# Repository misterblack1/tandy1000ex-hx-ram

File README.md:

# Tandy 1000 RAM Expansion

***Cheap*** *and **Simple** expansion board that only requires* <br>
*3 to 4 ICs and has been tested for **EX** and **HX** machines.*

*Designed by **[Adrian Black]**.*

<br>

<div align = center>

---

[![Button Video]][Video]   
[![Button PCB]][PCB]   
[![Button Schematic]][Schematic]   
[![Button Gerber]][Gerber]

---

<br>
<br>
<br>

![Preview]

<br>

⸢ *[Render]*  ⸥                                                                                           ⸢ *[Circuit]*  ⸥

</div>

<br>
<br>

## Assembly

*How to put the board together.*

<br>

### 3 ICs

If you bypass the  `74LS245`  with <br>
a jumper you can save one **IC**.

<br>

### LED

If you don't want the **LED**, you <br>
can leave it off as well as  `R3` .

<br>

### 74HCT

If you choose to use the  `74HCT` , you will <br>
just have to replace  `R1`  &  `R2`  with  `10kΩ` .

<br>
<br>

## Files

Created with **[KiCAD v5.1.4-1][KiCAD]**.

The uploaded files are of  `version 1.2` , with <br>
the fixes, talked about in the **[Video]**, applied.

<br>

<!----------------------------------------------------------------------------->

[Adrian Black]: https://github.com/misterblack1

[Video]: https://www.youtube.com/watch?v=l3RWOZX58A8
[KiCAD]: https://www.kicad.org/

[Schematic]: Resources/Schematics.pdf
[Preview]: Resources/Preview.png
[Circuit]: Resources/Circuit.png
[Render]: Resources/Render.png
[Gerber]: Gerbers
[PCB]: Source

<!-------------------------------[ Buttons ]----------------------------------->

[Button Schematic]: https://img.shields.io/badge/Schematic-006241?style=for-the-badge&logoColor=white&logo=StackShare
[Button Gerber]: https://img.shields.io/badge/Gerber-139BB4?style=for-the-badge&logoColor=white&logo=Stimulus
[Button Video]: https://img.shields.io/badge/Video-CD2640?style=for-the-badge&logoColor=white&logo=YouTube
[Button PCB]: https://img.shields.io/badge/PCB-314CB0?style=for-the-badge&logoColor=white&logo=tmux

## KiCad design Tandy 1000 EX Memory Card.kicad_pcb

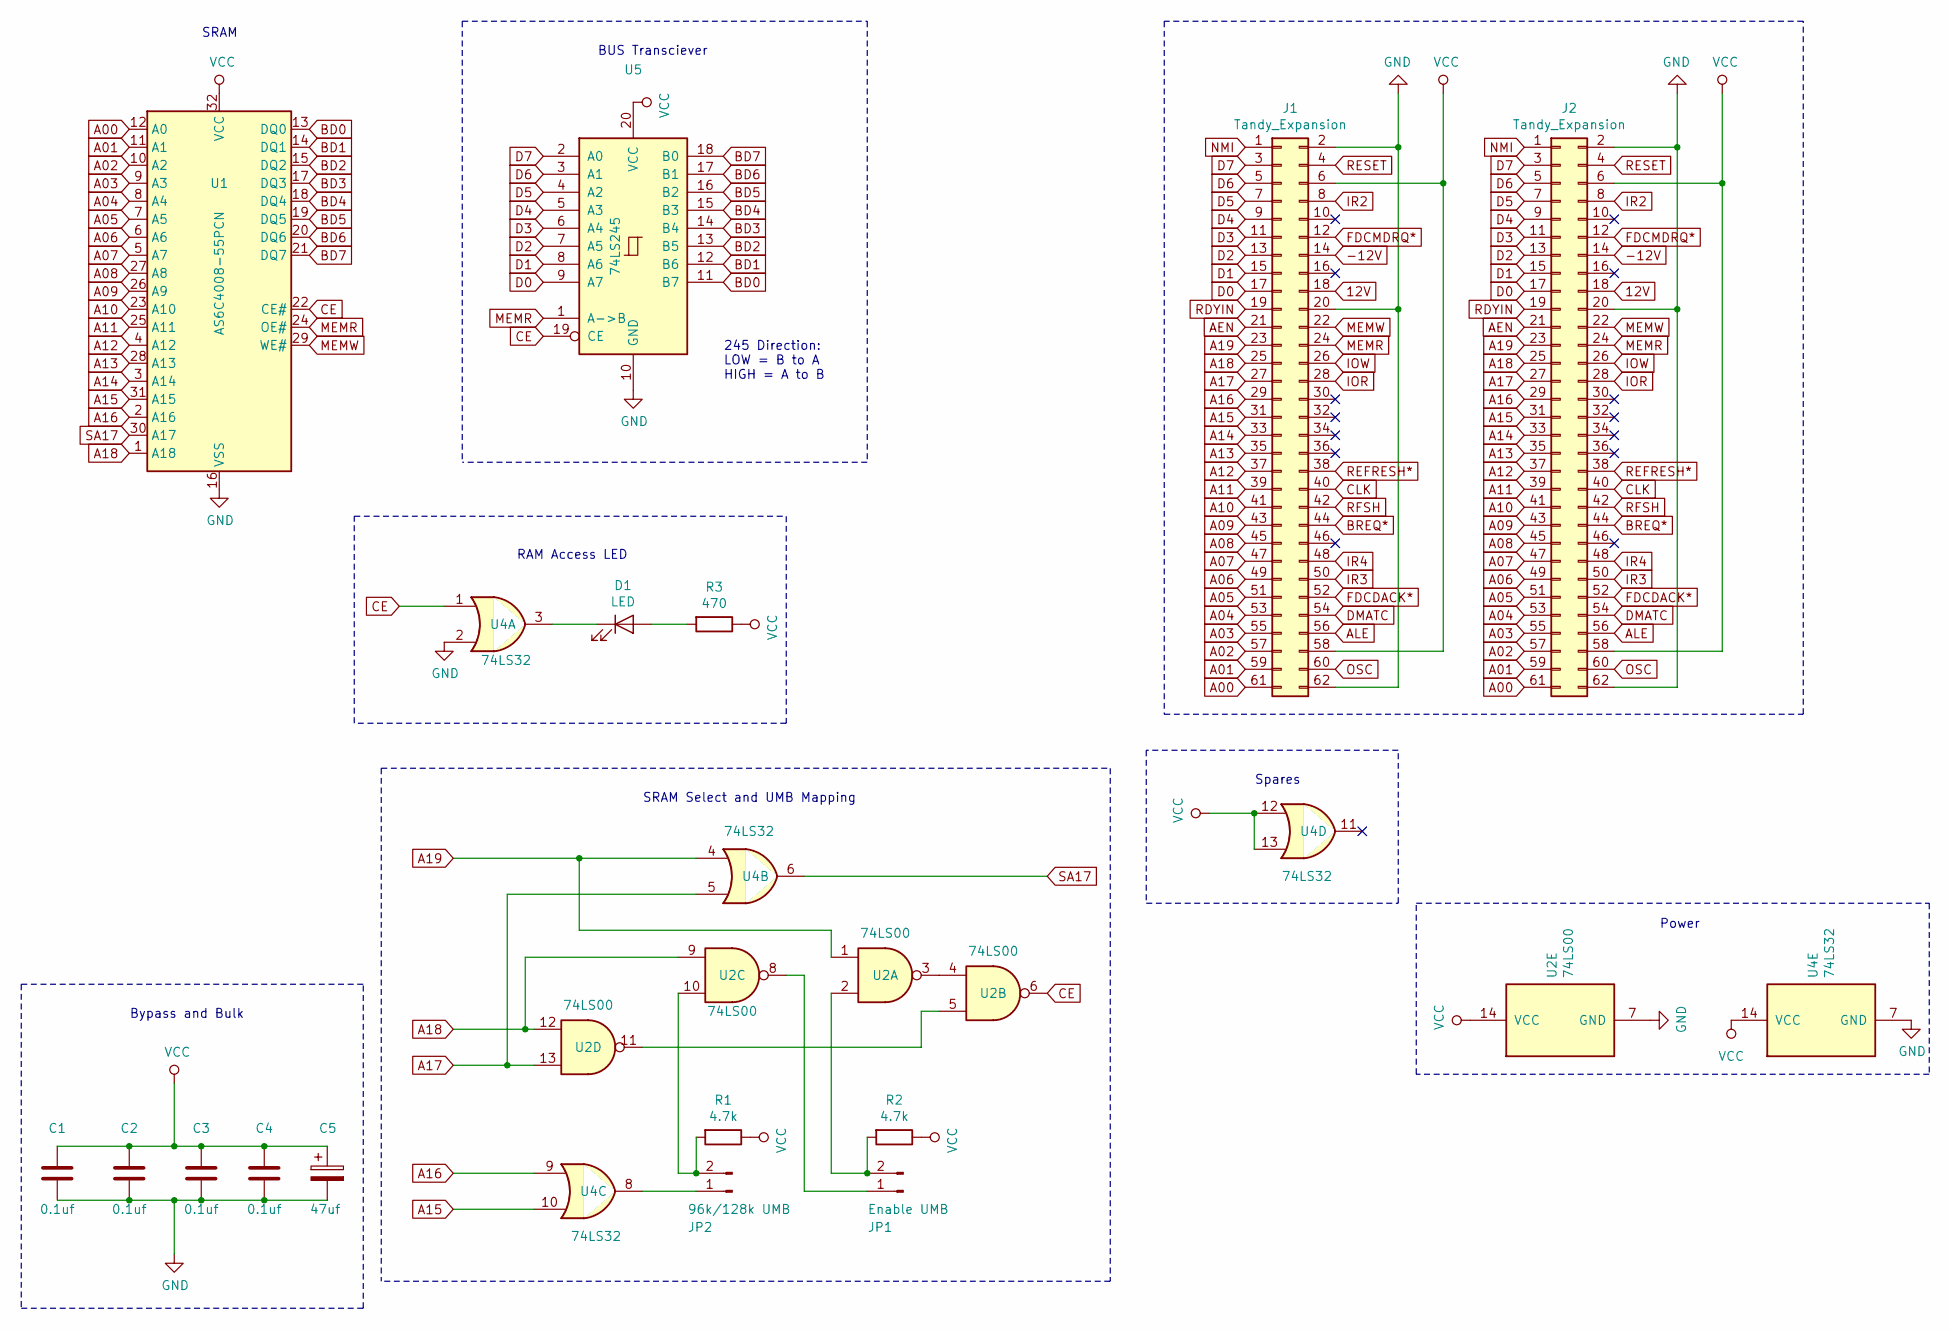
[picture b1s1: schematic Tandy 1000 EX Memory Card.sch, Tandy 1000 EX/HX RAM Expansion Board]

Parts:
C1, C2, C3, C4: 0.1uf; C_Rect_L4.0mm_W2.5mm_P2.50mm
C5: 47uf; CP_Radial_D4.0mm_P2.00mm
D1: LED; LED_D3.0mm
J1: Tandy_Expansion; PinSocket_2x31_P2.54mm_Vertical
J2: Tandy_Expansion; PinHeader_2x31_P2.54mm_Vertical
JP1: Enable UMB; PinSocket_1x02_P2.54mm_Vertical
JP2: 96k/128k UMB; PinHeader_1x02_P2.54mm_Vertical
R1, R2: 4.7k; R_Axial_DIN0207_L6.3mm_D2.5mm_P10.16mm_Horizontal
R3: 470; R_Axial_DIN0207_L6.3mm_D2.5mm_P10.16mm_Horizontal
U1: AS6C4008-55PCN; DIP-32_W15.24mm
U2: 74LS00; DIP-14_W7.62mm
U4: 74LS32; DIP-14_W7.62mm
U5: 74LS245; DIP-20_W7.62mm

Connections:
12V: J1.18, J2.18
-12V: J1.14, J2.14
A00: J1.61, J2.61, U1.12 (A0)
A01: J1.59, J2.59, U1.11 (A1)
A02: J1.57, J2.57, U1.10 (A2)
A03: J1.55, J2.55, U1.9 (A3)
A04: J1.53, J2.53, U1.8 (A4)
A05: J1.51, J2.51, U1.7 (A5)
A06: J1.49, J2.49, U1.6 (A6)
A07: J1.47, J2.47, U1.5 (A7)
A08: J1.45, J2.45, U1.27 (A8)
A09: J1.43, J2.43, U1.26 (A9)
A10: J1.41, J2.41, U1.23 (A10)
A11: J1.39, J2.39, U1.25 (A11)
A12: J1.37, J2.37, U1.4 (A12)
A13: J1.35, J2.35, U1.28 (A13)
A14: J1.33, J2.33, U1.3 (A14)
A15: J1.31, J2.31, U1.31 (A15), U4.10
A16: J1.29, J2.29, U1.2 (A16), U4.9
A17: J1.27, J2.27, U2.13, U4.5
A18: J1.25, J2.25, U1.1 (A18), U2.9, U2.12
A19: J1.23, J2.23, U2.1, U4.4
AEN: J1.21, J2.21
ALE: J1.56, J2.56
BD0: U1.13 (DQ0), U5.11 (B7)
BD1: U1.14 (DQ1), U5.12 (B6)
BD2: U1.15 (DQ2), U5.13 (B5)
BD3: U1.17 (DQ3), U5.14 (B4)
BD4: U1.18 (DQ4), U5.15 (B3)
BD5: U1.19 (DQ5), U5.16 (B2)
BD6: U1.20 (DQ6), U5.17 (B1)
BD7: U1.21 (DQ7), U5.18 (B0)
BREQ*: J1.44, J2.44
CE: U1.22 (CE#), U2.6, U4.1, U5.19 (CE)
CLK: J1.40, J2.40
D0: J1.17, J2.17, U5.9 (A7)
D1: J1.15, J2.15, U5.8 (A6)
D2: J1.13, J2.13, U5.7 (A5)
D3: J1.11, J2.11, U5.6 (A4)
D4: J1.9, J2.9, U5.5 (A3)
D5: J1.7, J2.7, U5.4 (A2)
D6: J1.5, J2.5, U5.3 (A1)
D7: J1.3, J2.3, U5.2 (A0)
DMATC: J1.54, J2.54
FDCDACK*: J1.52, J2.52
FDCMDRQ*: J1.12, J2.12
GND: C1.1, C2.1, C3.1, C4.1, C5.2, J1.2, J1.20, J1.62, J2.2, J2.20, J2.62, U1.16 (VSS), U2.7 (GND), U4.2, U4.7 (GND), U5.10 (GND)
IOR: J1.28, J2.28
IOW: J1.26, J2.26
IR2: J1.8, J2.8
IR3: J1.50, J2.50
IR4: J1.48, J2.48
MEMR: J1.24, J2.24, U1.24 (OE#), U5.1 (A->B)
MEMW: J1.22, J2.22, U1.29 (WE#)
NMI: J1.1, J2.1
unnamed: D1.1 (K), U4.3
unnamed: D1.2 (A), R3.2
unnamed: JP1.1, U2.8
unnamed: JP1.2, R2.2, U2.2
unnamed: JP2.1, U4.8
unnamed: JP2.2, R1.2, U2.10
unnamed: U2.3, U2.4
unnamed: U2.5, U2.11
OSC: J1.60, J2.60
RDYIN: J1.19, J2.19
REFRESH*: J1.38, J2.38
RESET: J1.4, J2.4
RFSH: J1.42, J2.42
SA17: U1.30 (A17), U4.6
VCC: C1.2, C2.2, C3.2, C4.2, C5.1, J1.6, J1.58, J2.6, J2.58, R1.1, R2.1, R3.1, U1.32 (VCC), U2.14 (VCC), U4.12, U4.13, U4.14 (VCC), U5.20 (VCC)

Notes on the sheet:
245 Direction: LOW = B to A HIGH = A to B
RAM Access LED
Spares
Power
Bypass and Bulk
SRAM
BUS Transciever
SRAM Select and UMB Mapping

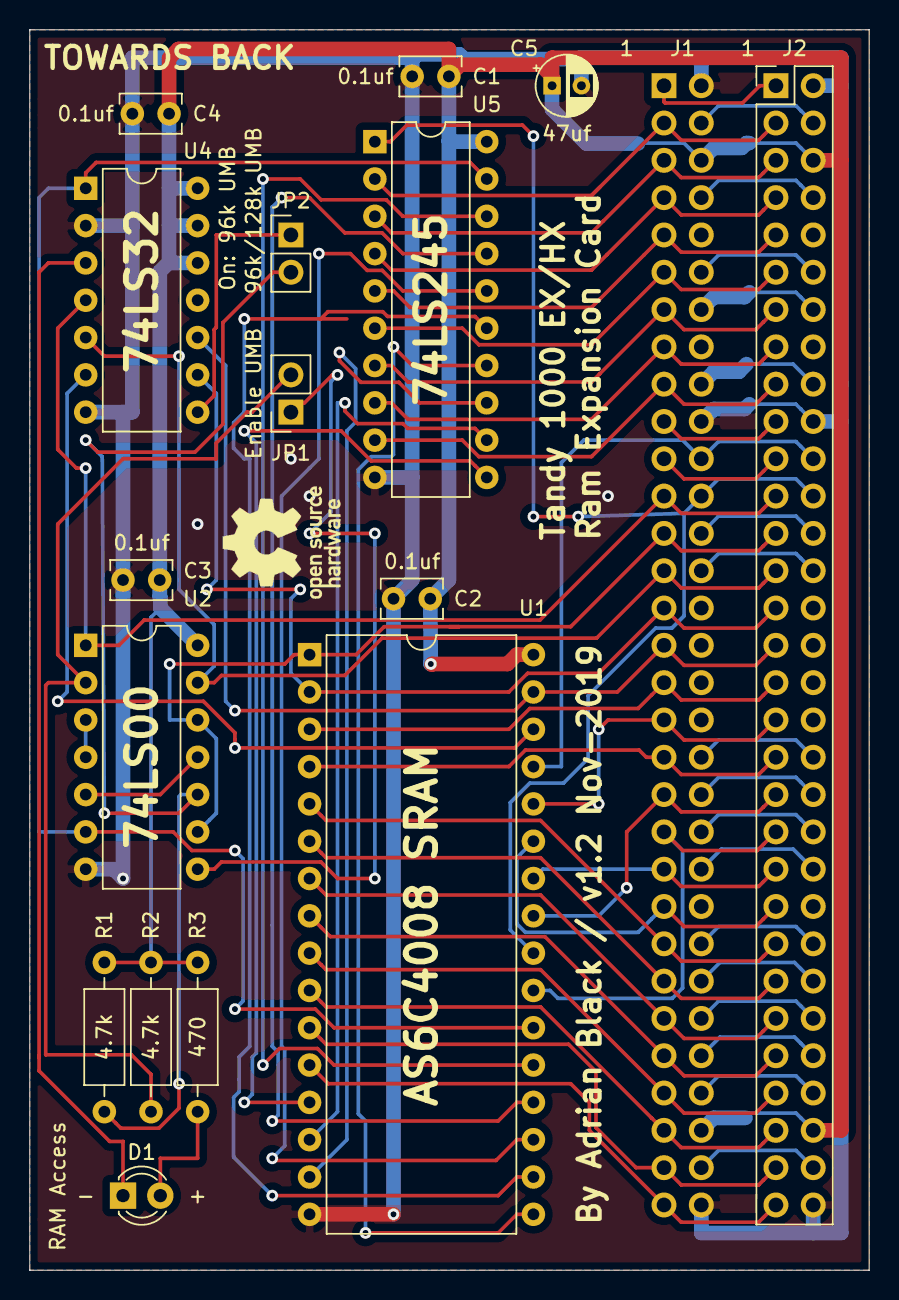
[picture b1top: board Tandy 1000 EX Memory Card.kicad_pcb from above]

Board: 2 copper layers, 57.2 x 84.5 mm, 17 parts (1 on the bottom side), 70 nets.

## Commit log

2019-11-03 Initial
2019-11-03 Initial
    Config.sys / Autoexec.bat and utilities needed to use UMB (upper memory blocks)
2019-11-04 Add YouTube Link
2019-11-04 Updated with OSHW Logo/License
2021-12-29 Added Preview
2021-12-29 Sorted Files
2021-12-29 Reworked README
2021-12-29 Additional Links | Side By Side Preview
2022-07-06 Updated Formatting
2022-07-06 Adjusted Spacing
